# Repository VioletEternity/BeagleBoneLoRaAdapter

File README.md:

# Dual LoRa module adapter for BeagleBone

This PCBA connects widely available LoRa modules based on Semtech [SX127x][] RFIC, such as [this module][module] ([archive][module-archive]) sold on Aliexpress for less than $3, to the Texas Instruments [BeagleBone][] family of single board computers.

[module]: https://www.aliexpress.com/item/32814250318.html
[module-archive]: https://archive.today/oJ4Fh
[sx127x]: https://www.semtech.com/products/wireless-rf/lora-connect
[beaglebone]: https://beaglebone.org

## Requirements

The module must have a size of 16 by 16 mm, and have 16 castellated pads with 2 mm spacing; for details, see the Kicad footprint. The module pinout must match the following, viewed from the top:

| Pin 1? | &nbsp;&nbsp;&nbsp;&nbsp;&nbsp;&nbsp;&nbsp;&nbsp;&nbsp;&nbsp;&nbsp;&nbsp;&nbsp;&nbsp;&nbsp;&nbsp;&nbsp;&nbsp;&nbsp;&nbsp;&nbsp;&nbsp;&nbsp;&nbsp;&nbsp;&nbsp;&nbsp;&nbsp;&nbsp;&nbsp;&nbsp;&nbsp;&nbsp; | &nbsp; |
| ------ | - | ------ |
| ANT    |   |    GND |
| GND    |   |   DIO5 |
| DIO3   |   | nRESET |
| DIO4   |   |    nCS |
| 3V3    |   |    SCK |
| DIO0   |   |   MOSI |
| DIO1   |   |   MISO |
| DIO2   |   |    GND |

These modules do not have a clearly marked pin 1, so the actual pinout may be rotated 180° compared to the above.

See also the [bill of materials](Mfg_Outputs/BeagleBoneLoRaAdapter.csv).

## Usage

### BeagleBone pinout

The following table lists the BeagleBone pins and their connections:

| Radio# | Function | BB pin | CPU pin   | 
|--------|----------|--------|-----------|
| radio0 | nRESET   | P9_15  | gpio1[16] |
| radio0 | IRQ      | P9_16  | gpio1[19] |
| radio0 | nCS      | P9_17  | gpio0[5]  |
| radio0 | SCK      | P9_22  | gpio0[2]  |
| radio0 | MOSI     | P9_18  | gpio0[4]  |
| radio0 | MISO     | P9_21  | gpio0[3]  |
| radio1 | nRESET   | P9_25  | gpio3[21] |
| radio1 | IRQ      | P9_27  | gpio3[19] |
| radio1 | nCS      | P9_28  | gpio3[17] |
| radio1 | SCK      | P9_31  | gpio3[14] |
| radio1 | MOSI     | P9_30  | gpio3[16] |
| radio1 | MISO     | P9_29  | gpio3[15] |

Radio 0 is connected to CS0 of SPI0, radio 1 is connected to CS0 of SPI1.

### BeagleBone pin mux configuration

To configure BeagleBone pins, run the following commands:

```shell
sudo modprobe spidev
sudo chown $USER /dev/spidev*

config-pin P9_15 gpio_pu
config-pin P9_16 gpio_pu
config-pin P9_17 spi_cs
config-pin P9_22 spi_sclk
config-pin P9_18 spi
config-pin P9_21 spi

config-pin P9_25 gpio_pu
config-pin P9_27 gpio_pu
config-pin P9_28 spi_cs
config-pin P9_31 spi_sclk
config-pin P9_30 spi
config-pin P9_29 spi
```

These commands were tested on Debian 12 (bookworm).

### Basic functional test

To perform a basic test of module functionality, install `spi-tools` and run the following commands:

```shell
echo '0: 4200' | xxd -r | spi-pipe -b 2 -d /dev/spidev0.0 | xxd
echo '0: 4200' | xxd -r | spi-pipe -b 2 -d /dev/spidev1.0 | xxd
```

Both commands should return the following output:

```
00000000: 0012                                     ..
```

The number `12` is the module ASIC revision.

### Full functional test

Steps for performing a full test of module functionality, including radio transmission and reception, will be provided later.

## Revision history

A1
: Initial revision

## Terms of distribution

The adapter is covered by the CERN-OHL-P (permissive) license. See [LICENSE.txt](LICENSE.txt) for details.

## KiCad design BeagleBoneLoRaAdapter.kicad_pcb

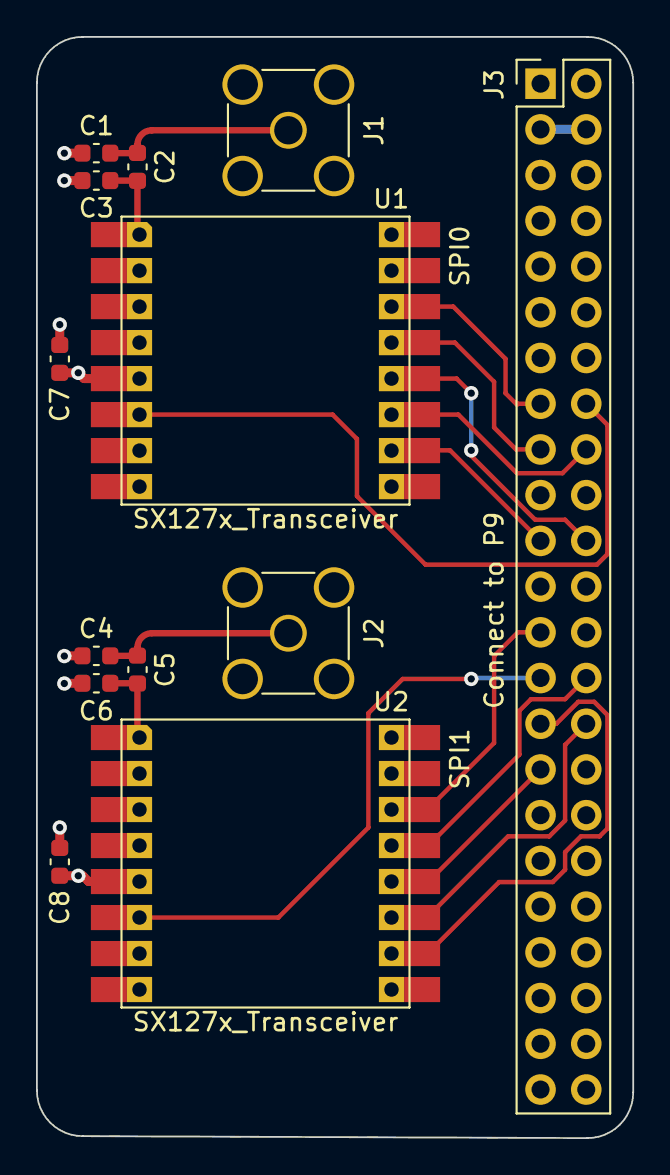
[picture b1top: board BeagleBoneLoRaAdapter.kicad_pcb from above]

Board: 4 copper layers, 33.1 x 61.2 mm, 13 parts (0 on the bottom side), 18 nets.

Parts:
C1, C3, C4, C6: DNP; C_0603_1608Metric
C2, C5: 220p; C_0603_1608Metric
C7, C8: 10u; C_0603_1608Metric
J1, J2: Conn_Coaxial; SMA_Cinch_142-0701_Vertical
J3: Conn_02x23_Odd_Even; PinHeader_2x23_P2.54mm_Vertical
U1, U2: SX127x_Transceiver; LoRaModule-16_16.0x16.0mm_Layout2x8_P2.0mm

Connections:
+3V3: C7.1, C8.1, J3.3, J3.4, U1.5 (VCC), U2.5 (VCC)
/IRQ0: J3.16, U1.6 (DIO0)
/IRQ1: J3.27, U2.6 (DIO0)
/MISO0: J3.21, U1.10 (MISO)
/MISO1: J3.29, U2.10 (MISO)
/MOSI0: J3.18, U1.11 (MOSI)
/MOSI1: J3.30, U2.11 (MOSI)
/SCK0: J3.22, U1.12 (SCK)
/SCK1: J3.31, U2.12 (SCK)
/~CS0: J3.17, U1.13 (~CS)
/~CS1: J3.28, U2.13 (~CS)
/~RESET0: J3.15, U1.14 (~RESET)
/~RESET1: J3.25, U2.14 (~RESET)
GND: C1.1, C3.2, C4.1, C6.2, C7.2, C8.2, J1.2 (Ext), J2.2 (Ext), J3.1, J3.2, J3.43, J3.44, J3.45, J3.46, U1.2 (GND), U1.9 (GND), U1.16 (GND), U2.2 (GND), U2.9 (GND), U2.16 (GND)
unnamed: C1.2, C2.1, J1.1 (In)
unnamed: C2.2, C3.1, U1.1 (ANT)
unnamed: C4.2, C5.1, J2.1 (In)
unnamed: C5.2, C6.1, U2.1 (ANT)

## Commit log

2023-04-14 Rev A1
2023-04-24 Add Px_y pin names on schematic
2023-04-24 Add schematic to mfg outputs
2023-04-24 Reexport gerbers with solder mask substracted from silk
2023-04-24 Add BOM
2023-04-24 Add documentation
2023-04-24 Minor fixes
2023-04-24 Fix typo in README
2024-05-25 Update commands in README for Debian 12.
